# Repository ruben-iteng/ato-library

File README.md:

<!-- This document is autogenerated - Do not edit manually!! -->

# ato-library

This is a monorepo for various [ato](https://docs.atopile.io) and [fabll](https://docs.atopile.io/atopile/guides/faebryk) packages for your projects made with [atopile](https://www.github.com/atopile/atopile) that can be found in the official [atopile package registry](https://packages.atopile.io/)

## Available Packages

| Package | Modules | Description | Version |
|---------|---------|-------------|---------|
| [analog-devices-max14778](packages/analog-devices-max14778/README.md) | 1 module | Analog Devices MAX14778 dual 4:1 +/-25V above/below the rails analog multiplexer | 0.1.2 |
|  | analog_devices_max14778_driver | Analog Devices MAX14778 dual 4:1 +/-25V above/below the rails analog multiplexer | |
| [connectors](packages/connectors/README.md) | 4 modules | Miscellaneous connectors | 0.2.3 |
|  | dual_banana_connectors | Dual banana connectors (Red and Black) with 3/4\" (19.05mm) spacing. | |
|  | qwiic_vertical | Vertical QWIIC connector<br>    https://www.sparkfun.com/qwiic | |
|  | qwiic_horizontal | Horizontal QWIIC connector<br>    https://www.sparkfun.com/qwiic | |
|  | fan_connector | Connector for standard 4-pin 12v computer fans<br>    - 12V<br>    - Tach<br>    - PWM | |
| [dcdc-converters](packages/dcdc-converters/README.md) | 2 modules | DCDC converters | 0.2.2 |
|  | b0505s1wr3 | EVISUN B0505S-1WR3 5V to 5V isolated DCDC converter with shortcircuit protection<br>    - 5V input<br>    - 5V output<br>    - 1W power rating | |
|  | mpm3610-12vin-5vout | MPM3610 with component parameters optimized for 12V input and 5V output | |
| [debug-interfaces](packages/debug-interfaces/README.md) | 4 modules | SWD and tag connect headers for programming and debugging | 0.2.3 |
|  | arm_cortex_m_debug_header | 10 pin debug header with SWD pinout according to ARM Cortex M debug specification<br>    https://documentation-service.arm.com/static/5fce6c49e167456a35b36af1 | |
|  | swd_tc2030_idc_nl | Tag-Connect TC2030-IDC-NL (6-pin) landing pattern with SWD pinout | |
|  | swd_tc2030_idc_fp | Tag-Connect TC2030-IDC-FP (6-pin) landing pattern with SWD pinout | |
|  | segger_jlink_compact | SEGGER J-Link compact PCBA mount | |
| [esp32c3](packages/esp32c3/README.md) | 2 modules | ESP32 C3 microcontroller | 0.2.3 |
|  | esp32_c3_mini_driver | ESP32 S3 WROOM-1 module with build-in antenna and supporting components | |
|  | esp32_c3_mini_ufl_driver | ESP32 S3 WROOM-1 module with u.fl antenna connector and supporting components | |
| [esp32s3](packages/esp32s3/README.md) | 1 module | ESP32 S3 microcontroller | 0.2.2 |
|  | esp32_s3_wroom_driver | ESP32 S3 WROOM-1 module with build-in antenna and supporting components<br>    - 32MB flash<br>    - 2MB PSRAM | |
| [ina228](packages/ina228/README.md) | 1 module | INA228 low voltage power monitor with I2C interface | 0.2.2 |
|  | ina228 | INA228 85-V, 20-bit, ultra-precise, I2C output<br>    current/voltage/power/energy/charge monitor with alert | |
| [ldos](packages/ldos/README.md) | 1 module | Various Low Dropout Regulators (LDOs) | 0.2.3 |
|  | 5v_to_3v3 | 5V to 3.3V 600mA (max 1100mA) LDO | |
| [leds](packages/leds/README.md) | 2 modules | Various (addressable) LED components and modules | 0.2.2 |
|  | addressable_led_connector_driver | XT30 connector with 2 additional data pins.<br>    Wired for connecting to addressable LED strips. | |
|  | addressable_led_driver | Addressable LED with decoupling capacitors.<br><br>    Usage:<br>    from "ruben-iteng/ato-library/leds/addressable_leds.ato" import AddressableLED<br><br>    module MyProject:<br>        ...<br>        leds = new AddressableLED[3]<br><br>        power = new ElectricPower<br>        data_in = new ElectricLogic<br><br>        for led in leds:<br>            led -> WS2812B_5050_Black<br>            led.power ~ power<br><br>        data_in ~> leds[0] ~> leds[1] ~> leds[2] | |
| [logic](packages/logic/README.md) | 5 modules | Digital logic related components and modules | 0.2.2 |
|  | aip74lvc1t45_driver | Single channel bidirectional buffer.<br>    1.2V-5.5V logic levels.<br>    SOT-23-6 | |
|  | sn74lvc2g34dbvrumw_driver | UMWYoutai Semiconductor Co., Ltd.<br>    74LVC2G34 Dual buffer. | |
|  | sn74lvc3g14dc_driver | - | |
|  | iso1540_driver | ISO1540 low-power bidirectional I2C isolators.<br>    - 3.0V to 5.5V power and signal levels<br>    - up to 100Mhz I2C | |
|  | sn74cb3q3251pwr_driver | Texas Instruments SN74CB3Q3251PWR<br>    1 to/from 8 FET multiplexer/demultiplexer<br>    2.5V/3.3V low-voltage high-bandwidth bus switch | |
| [logos](packages/logos/README.md) | 1 module | Various logos | 0.2.0 |
|  | faebryk_logo_8x9mm | faebryk Logo 8x9mm | |
| [microchip-emc2101](packages/microchip-emc2101/README.md) | 1 module | Microchip EMC2101 fan driver | 0.1.2 |
|  | microchip_emc2101_driver | MicrochipEMC2101 fan driver<br>    Automatic Beta Compensation<br>    - Resistance Error Correction<br>    - Self-programming with available SMBus compatible EEPROM<br>    - Selectable PWM or DAC fan driver output<br>    - Temperature Monitors<br>      - External channel ±1°C accuracy<br>      - Internal channel ±2°C accuracy<br>    - 3.3 Volt Operation (5 Volt Tolerant Input Buffers)<br>    - SMBus 2.0 Compliant Interface, supports TIMEOUT | |
| [nxp_semiconductors-pca95xx](packages/nxp_semiconductors-pca95xx/README.md) | 7 modules | NXP Semiconductors PCA95xx family of I2C I/O expanders | 0.2.0 |
|  | pca9554pw_driver | NXP Semiconductors PCA9554 TSSOP16 package | |
|  | pca9554apw_driver | NXP Semiconductors PCA9554A TSSOP16 package | |
|  | pca9554abs_driver | NXP Semiconductors PCA9554A HVQFN16(4x4mm) package | |
|  | pca9554bs_driver | NXP Semiconductors PCA9554 HVQFN16(4x4mm) package | |
|  | pca9536d_driver | NXP Semiconductors PCA9536D SO-8 package | |
|  | pca9536tk_driver | NXP Semiconductors PCA9536TK HVSON-8 package | |
|  | pca9536dp_driver | NXP Semiconductors PCA9536DP TSSOP-8 package | |
| [relays](packages/relays/README.md) | 3 modules | Relay modules | 0.2.2 |
|  | driven_dpdt_bistable_relay | Bistable DPDT relay with driver and indicator LEDs<br>    - 5V coil power<br>    - 5V/3.3V logic power<br>    - 2A contact carry current<br>    - TC118S DC motor driver (H-bridge) as relay driver | |
|  | driven_dpdt_bistable_relay_push_terminal | DrivenDPDTBistableRelay with push terminal | |
|  | dc_motor_driver | Shenzhen Fuman Elec TC118S dc motor driver<br>    - Single-channel built-in high-power MOS full-bridge driver<br>    - Supports forward, reverse, stop, and brake functions<br>    - Built-in efficient thermal response and thermal protection<br>    - Low on-resistance (1.6Ω)<br>    - Maximum continuous output current: 1.8A, peak current: 2.5A | |
| [rohm_semiconductor_bh1750fvi](packages/rohm_semiconductor_bh1750fvi/README.md) | 1 module | ROHM Semiconductor BH1750FVI-TR Digital Ambient Light Sensor with I2C interface | 0.1.1 |
|  | bh1750_driver | Digital ambient light sensor with I2C interface<br><br>    - I2C bus Interface (f/s Mode Support)<br>    - Spectral responsibility is approximately human eye response<br>    - Illuminance to Digital Converter<br>    - Wide range and High resolution (1 - 65535 lx)<br>    - Low Current by power down function<br>    - 50Hz/60Hz Light noise reject-function<br>    - 1.8V Logic input interface<br>    - No need any external parts<br>    - Light source dependency is little (Incandescent Lamp, Fluorescent Lamp, Halogen Lamp, White LED, Sun Light)<br>    - It is possible to select 2 type of I2C slave-address<br>    - Adjustable measurement result for influence of optical window (It is possible to detect min. 0.11 lx, max. 100000 lx by using this function)<br>    - Small measurement variation (+/- 20%)<br>    - The influence of infrared is very small | |
| [rs485](packages/rs485/README.md) | 4 modules | RS485 related modules | 0.2.3 |
|  | bus_protection | RS485 bus protection.<br>    - Overvoltage protection<br>    - Overcurrent protection<br>    - Common mode filter<br>    - Termination resistor<br>    - ESD protection<br>    - Lightning protection<br><br>    based on: https://www.mornsun-power.com/public/uploads/pdf/TD(H)541S485H.pdf | |
|  | maxlinear_sp3485en_driver | Simple UART to RS485 converter.<br>    UART and write enable interface in, RS485 interface out. | |
|  | analog_devices_adm2587ebrwz_driver | Isolated UART to half duplex RS485 interface | |
|  | chipanalog_is2092a_driver | Isolated powered UART to RS485 transceiver design block.<br>    - 3.3V or 5V logic power<br>    - 3.3V or 5V module power<br>    - 0.5 Mbps UART<br>    - Read enable/write enable input<br>    - RS485 half duplex<br>    - ANSI/ESDA/JEDEC JS-001 ESD protection<br>    - JESD22-C101 CDM protection | |
| [switches](packages/switches/README.md) | 2 modules | Rotary encoders, switches, and other switch like components and modules | 0.1.4 |
|  | rotary_encoder_advanced | Rotary encoder + switchwith debouncing and hysteresis.<br><br>    Specialize the rotary encoder in your application:<br>    rot_encoder = new RotaryEncoderAdvanced<br>    rot_encoder.encoder -> ALPSALPINE_EC11E15244B2 | |
|  | test | Test module for buttons | |
| [texas_instruments_lm66200](packages/texas_instruments_lm66200/README.md) | 1 module | Texas Instruments LM66200DRLR 1.6 V to 5 V, 2.5-A Dual Ideal Diode With Automatic Switchover | 0.1.1 |
|  | lm66200 | Texas Instruments LM66200 dual ideal diode with automatic switchover.<br>    - Input voltage range: 1.6 V to 5.5 V<br>    - Maximum continuous current: 2.5 A<br>    - On-resistance: 40 mΩ (typical)<br>    - Standby current: 50 nA (typical)<br>    - Quiescent current: 1.32 μA (typical)<br>    - Automatic diode switchover<br>    - Controlled output slew rate:<br>        - 1.3 ms (typical) at 3.3 V.<br>    - Reverse current blocking when VOUT > VINx.<br>    - Thermal shutdown. | |
| [usb](packages/usb/README.md) | 4 modules | USB connectors and circuitry | 0.3.1 |
|  | usb_2_0_type_c_data_power_vertical_connector | USB 2.0 Type-C connector<br>    - 5V PD compatible<br>    - ESD protection<br>    - Fuse [500mA(hold), 1A(trip)]<br>    - Vertical USB Type-C connector | |
|  | usb_2_0_type_c_data_power_horizontal_connector | USB 2.0 Type-C connector<br>    - 5V PD compatible<br>    - ESD protection<br>    - Fuse [500mA(hold), 1A(trip)]<br>    - Horizontal USB Type-C connector | |
|  | usb_pd_power_sink_horizontal_connector | USB PD power sink with Horizontal Type-C connector<br><br>    Set the requested PD voltages as follows:<br>    9V  -> resistance = 6.8kohm<br>    12V -> resistance = 24kohm<br>    15V -> resistance = 56kohm<br>    20V -> resistance = DNP<br>    pd_sink = new USBPDPowerSink<br>    pd_sink.pd_trigger.voltage_set_resistor.resistance = 56kohm +/- 1% | |
|  | usb_pd_power_sink_vertical_connector | USB PD power sink with Vertical Type-C connector<br><br>    Set the requested PD voltages as follows:<br>    9V  -> resistance = 6.8kohm<br>    12V -> resistance = 24kohm<br>    15V -> resistance = 56kohm<br>    20V -> resistance = DNP<br>    pd_sink = new USBPDPowerSink<br>    pd_sink.pd_trigger.voltage_set_resistor.resistance = 56kohm +/- 1% | |

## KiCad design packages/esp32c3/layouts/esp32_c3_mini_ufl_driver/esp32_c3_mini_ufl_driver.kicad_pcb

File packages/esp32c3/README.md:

# esp32c3

ESP32 C3 microcontroller

## Package Information

- Version: 0.2.3
- Total Modules: 2
- Author(s): Ruben Baldewsing
- License: MIT
- Homepage: https://github.com/ruben-iteng/ato-library/blob/main/packages/esp32c3/README.md

## Available Modules

### Module List

| Image | Module | Description |
|-------|--------|-------------|
|| esp32_c3_mini_driver | ESP32 S3 WROOM-1 module with build-in antenna and supporting components |
|| esp32_c3_mini_ufl_driver | ESP32 S3 WROOM-1 module with u.fl antenna connector and supporting components |

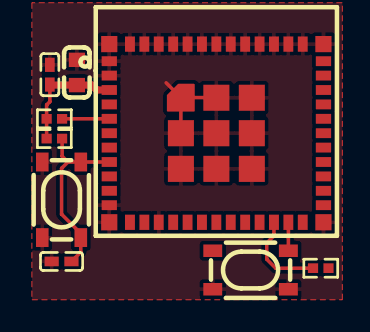
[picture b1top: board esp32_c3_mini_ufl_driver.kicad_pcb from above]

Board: 2 copper layers, 9 parts (0 on the bottom side), 6 nets.

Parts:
C1: 22µF ±20% 6.3V X5R; C0603
C2: 100nF ±10% 16V X7R; C0402
C3: 1µF ±10% 25V X5R; C0402
R1, R2, R3: 10kΩ ±1% 62.5mW; R0402
U1, U3: KEY-SMD_4P-L4.2-W3.2-P2.20-LS4.6
U2: WIFIM-SMD_ESP32-C3-MINI-MINI-1U

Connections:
EN: C3.1, R3.2, U2.8, U3.1, U3.2
IO2: R1.1, U2.5
IO9: U1.1, U1.2, U2.23
gnd: C1.2, C2.2, C3.2, U1.3, U1.4, U2.1, U2.2, U2.11, U2.14, U2.36, U2.37, U2.38, U2.39, U2.40, U2.41, U2.42, U2.43, U2.44, U2.45, U2.46, U2.47, U2.48, U2.49, U2.50, U2.51, U2.52, U2.53, U3.3, U3.4
hv: C1.1, C2.1, R1.2, R2.2, R3.1, U2.3
line: R2.1, U2.22

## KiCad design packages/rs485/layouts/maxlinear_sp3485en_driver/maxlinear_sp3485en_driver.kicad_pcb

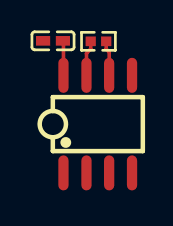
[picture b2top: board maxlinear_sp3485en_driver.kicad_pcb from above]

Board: 2 copper layers, 3 parts (0 on the bottom side), 4 nets.

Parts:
C1: 100nF ±10% 16V X7R; C0402
R1: 120Ω ±1% 62.5mW; R0402
U1: SOIC-8_L5.0-W4.0-P1.27-LS6.0-BL

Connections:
A: R1.1, U1.6
B: R1.2, U1.7
VCC: C1.1, U1.8
gnd: C1.2, U1.5

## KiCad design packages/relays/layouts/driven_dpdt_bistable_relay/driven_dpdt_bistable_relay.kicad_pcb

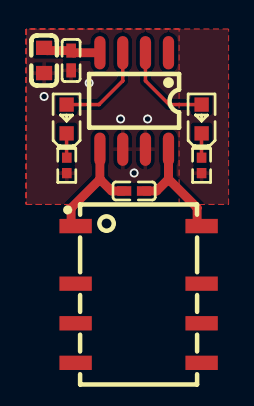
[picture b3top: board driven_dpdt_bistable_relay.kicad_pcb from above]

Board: 2 copper layers, 9 parts (0 on the bottom side), 8 nets.

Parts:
C1: 100nF ±10% 16V X7R; C0402
C2: 4.7µF ±10% 16V X5R; C0603
C3: 100pF ±5% 50V C0G; C0402
LED1, LED2: LED0603-RD
R1, R2: 10kΩ ±1% 62.5mW; R0402
U1: SOP-8_L4.9-W3.9-P1.27-LS6.0-BL
U2: RELAY-SMD_G6KU-2F-Y

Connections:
OUTA: C3.1, U1.8, U2.8
anode: LED2.2, U1.3
anode-1: LED1.2, U1.2
cathode: LED2.1, R2.1
cathode-1: LED1.1, R1.1
gnd: C1.2, C2.2, R1.2, R2.2, U1.6, U1.7
gnd-1: C3.2, U1.5, U2.1
hv: C1.1, C2.1, U1.4

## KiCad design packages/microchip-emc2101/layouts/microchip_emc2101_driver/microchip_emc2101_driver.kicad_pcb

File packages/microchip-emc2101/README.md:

# microchip-emc2101

Microchip EMC2101 fan driver

## Package Information

- Version: 0.1.2
- Total Modules: 1
- Author(s): Ruben Baldewsing
- License: MIT
- Homepage: https://github.com/ruben-iteng/ato-library/blob/main/packages/microchip-emc2101/README.md

## Available Modules

### Module List

| Image | Module | Description |
|-------|--------|-------------|
|| microchip_emc2101_driver | MicrochipEMC2101 fan driver<br>    Automatic Beta Compensation<br>    - Resistance Error Correction<br>    - Self-programming with available SMBus compatible EEPROM<br>    - Selectable PWM or DAC fan driver output<br>    - Temperature Monitors<br>      - External channel ±1°C accuracy<br>      - Internal channel ±2°C accuracy<br>    - 3.3 Volt Operation (5 Volt Tolerant Input Buffers)<br>    - SMBus 2.0 Compliant Interface, supports TIMEOUT |

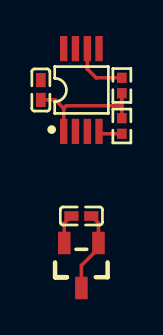
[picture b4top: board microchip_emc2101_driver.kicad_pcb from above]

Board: 2 copper layers, 6 parts (0 on the bottom side), 6 nets.

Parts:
C1: 100nF ±10% 16V X7R; C0402
C2: 2.2nF ±10% 50V X7R; C0402
Q1: SOT-23-3_L2.9-W1.3-P1.90-LS2.4-TR
R1, R2: 10kΩ ±1% 62.5mW; R0402
U1: MSOP-8_L3.0-W3.0-P0.65-LS4.9-BL

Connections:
DN: C2.1, Q1.2, Q1.3, U1.3
DP: C2.2, Q1.1, U1.2
FAN: R1.1, U1.4
VDD: C1.1, R1.2, R2.2, U1.1
gnd: C1.2, U1.5
nALERT_TACH: R2.1, U1.6

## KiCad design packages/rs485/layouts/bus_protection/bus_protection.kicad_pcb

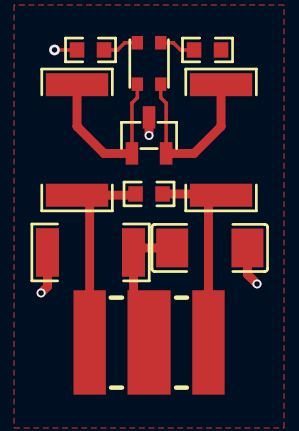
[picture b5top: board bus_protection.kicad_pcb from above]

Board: 2 copper layers, 10 parts (0 on the bottom side), 8 nets.

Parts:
C1: 1nF ±10% 2kV X7R; C1808
FL1: FILTER-SMD_4P-L2.5-W2.0-BL
GDT1: DIO-DT-SMD_L7.2-W5.0
R1, R2: 2.7Ω ±5% 1W; R2512
R3: 1MΩ ±1% 750mW; R2010
R4, R5: 390Ω ±1% 100mW; R0603
R6: 120Ω ±1% 100mW; R0603
U1: SOT-23-3_L2.9-W1.3-P1.90-LS2.4-BR

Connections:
earth: C1.2, GDT1.2, R3.2
gnd: C1.1, R3.1, R5.2, U1.3
line: FL1.4, R5.1
line-1: FL1.2, R1.1, U1.2
line-2: FL1.3, R4.1
line-3: FL1.1, R2.1, U1.1
tube_1: GDT1.1, R2.2, R6.1
tube_2: GDT1.3, R1.2, R6.2

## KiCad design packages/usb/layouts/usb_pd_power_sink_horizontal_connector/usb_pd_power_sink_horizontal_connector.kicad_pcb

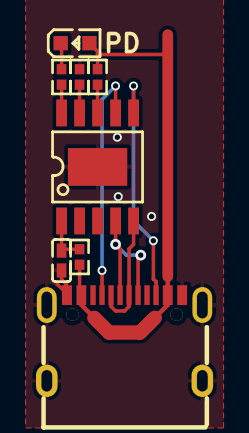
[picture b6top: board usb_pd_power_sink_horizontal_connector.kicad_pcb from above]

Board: 2 copper layers, 8 parts (0 on the bottom side), 11 nets.

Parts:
C1: 1µF ±10% 25V X5R; C0402
LED1: LED0603-RD
R1, R2, R4: 10kΩ ±1% 62.5mW; R0402
R3: 1kΩ ±1% 62.5mW; R0402
U1: ESSOP-10_L4.9-W3.9-P1.0-LS6.0-TL-EP
X1: USB-C-SMD_TYPE-C-6PIN-2MD-073

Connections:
anode: LED1.2, R2.1, R3.1, X1.2, X1.11
cathode: LED1.1, R1.1
gnd: C1.2, R4.2, U1.11, X1.1, X1.12, X1.13, X1.14
hv: C1.1, R3.2, U1.1
line: U1.7, X1.4
line-1: U1.6, X1.10
line-4: U1.5, X1.5, X1.7
line-5: U1.4, X1.6, X1.8
pd_trigger-gnd: R1.2, U1.10
pd_trigger-line: R4.1, U1.9
pd_trigger-line-1: R2.2, U1.8

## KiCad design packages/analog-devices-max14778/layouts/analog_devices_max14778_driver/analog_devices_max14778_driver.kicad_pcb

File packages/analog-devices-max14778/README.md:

# analog-devices-max14778

Analog Devices MAX14778 dual 4:1 +/-25V above/below the rails analog multiplexer

## Package Information

- Version: 0.1.2
- Total Modules: 1
- Author(s): Ruben Baldewsing
- License: MIT
- Homepage: https://github.com/ruben-iteng/ato-library/blob/main/packages/analog-devices-max14778/README.md

## Available Modules

### Module List

| Image | Module | Description |
|-------|--------|-------------|
|| analog_devices_max14778_driver | Analog Devices MAX14778 dual 4:1 +/-25V above/below the rails analog multiplexer |

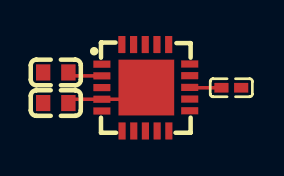
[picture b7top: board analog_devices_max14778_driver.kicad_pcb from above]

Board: 2 copper layers, 4 parts (0 on the bottom side), 4 nets.

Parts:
C1: 100nF ±10% 16V X7R; C0402
C2, C3: 100nF ±10% 100V X7R; C0603
U1: TQFN-20_L5.0-W5.0-P0.65-TL-EP3.1

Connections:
EP: C2.1, U1.4, U1.21
VP: C3.1, U1.2
gnd: C1.2, C2.2, C3.2, U1.3
hv: C1.1, U1.13

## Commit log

2025-04-13 Setup basics
2025-04-13 Add relays package
2025-04-13 Add build all script from atopile/packages
2025-04-13 Add debug connectors package
2025-04-13 Use Jinja2 for README template
    - Auto gen package readme
2025-04-13 Add package info to README
2025-04-18 Add explanation of the hooks
2025-04-18 Parse docstrings of python based modules
2025-04-18 Add new packages
    - debug interfaces
    - connectors
    - ina228
    - rs485
    - relays
2025-04-22 Bump required atopile version
2025-04-22 Fix pulldown on RE pins
2025-04-22 ignore more common files and artifacts
2025-04-22 Add logo package
2025-04-22 Add LDOs package
2025-04-22 Add USB2.0 Type-C interface to connector package
2025-04-22 Update build script and regenerate outputs
2025-04-27 Add ESP32S3, BM9002, Logic; Various naming updates and splitting of packages
2025-04-27 Add image rendering
2025-04-27 Fix pre-commit hook to run with uv
2025-04-27 Fix files to run hook on
2025-04-27 Generate images and READMEs
2025-04-27 Also regenerate READMEs when md templates changed
2025-04-27 Don't generate board renders with pre-commit hook.
    Then change every time they are generated
2025-04-27 Fix image size
2025-04-29 Update author name
2025-04-29 Remove connectors and replace with leds package
2025-04-29 rename bm9002 package
2025-04-29 Build all packages without designators on silkscreen.
    Also disable fail_on_drc and enable keep_picked_parts for build
2025-04-29 Change to alpha version
2025-04-29 Update version
2025-04-29 Add publishing workflow
2025-04-29 Update templates with abs reference to images as a short-term hack for getting them in the package manager
2025-04-29 Update READMEs
2025-05-01 Remove pull resistor (should not be part of the tranceiver)
2025-05-01 Fix publish if build fails
2025-05-01 Fix publish on failed build & fix pull resistor that should not be there (#2)
    * Remove pull resistor (should not be part of the tranceiver)
    * Fix publish if build fails
2025-05-01 [Publish] Fix image links and rebuild
2025-05-01 Don't run the workflow on draft PRs
2025-05-02 Bump version
2025-05-02 Rebuild modules
2025-05-02 Generate documentation
2025-05-02 Work around bad atopile net handling
    Mannually remove net number gap in pcb file and rebuild
2025-05-02 try with keep netnames enabled
2025-05-02 Don't run the workflow on draft PRs (#4)
2025-05-02 [Publish] Rebuild modules (with no dep on upstream atopile pr) (#5)
    * Fixes image link on published packages
2025-05-02 Add DrivenDPDTBistableRelayScrewTerminal
2025-05-05 Add seperate manually triggered publish workflow. Build workflow always runs (except on draft PR)
2025-05-06 Add seperate manually triggered publish workflow. Build workflow always runs (except on draft PR) (#7)
2025-05-06 Change name and update layout
2025-05-06 [Publish] Driven DPDT bistable-relay with push in terminal (#6)
2025-05-06 Add Rotaty encoder with signal cleaning, I2C isolator, and logic schmitt trigger
2025-05-06 Add Rotaty encoder with signal cleaning, I2C isolator, and logic schmitt trigger (#8)
2025-05-09 Add USB PD trigger
2025-05-09 Add USB PD trigger (#9)
2025-05-09 Update with new ato 0.7.x features
2025-05-09 Update with new ato 0.7.x features (#10)
2025-05-09 Add various addressable LEDs
2025-05-09 Add various addressable LEDs (#11)
2025-05-09 Rebuild logic package
2025-05-09 Add updated docs for logic package
2025-05-09 Rebuild relays package
2025-05-09 Rebuild usb package
2025-05-09 Rebuild switches package
2025-05-09 Rebuild rs485 package
2025-05-09 Add option to specify package to doc generator
2025-05-09 Add updated docs for rs485 package
2025-05-09 Update main README
2025-05-09 Rebuild modules frozen (#12)
    * Rebuild logic package
    * Add updated docs for logic package
    * Rebuild relays package
    * Rebuild usb package
    * Rebuild switches package
    * Rebuild rs485 package
2025-05-10 Use markdown instead of html for images in READMEs
2025-05-10 Regenerate READMEs and bump versions
2025-05-10 Fix: images for package registry (#13)
    * Use markdown instead of html for images in READMEs
    * Regenerate READMEs and bump versions
2025-05-10 Add DCDC converters package
2025-05-10 Add misc connectors package
2025-05-11 Update LDOs package
2025-05-11 Add QWIIC to connector package
2025-05-11 Add dual buffer to logic package
2025-05-12 add missing connection and remove test file
2025-05-12 Clean up package
2025-05-12 Update logos package
2025-05-12 Update RS485 protection layout
2025-05-12 Update rotary encoder advanced layout
2025-05-12 Update switches package readme
2025-05-12 Add various new packages (#14)
    Add:
    - DCDC converters
    - Connectors
    Update:
    - logic
    - add dual buffer
2025-05-12 Fix missing connection between JTAG and reset (enable)
2025-05-12 Fix missing connection between JTAG and reset (enable) (#15)
2025-05-13 Add isolated and powered RS485 tranceiver
2025-05-13 Add isolated and powered RS485 tranceiver (#16)
2025-05-13 Add ESP32C3 package
2025-05-13 Connect extra gnd pins
2025-05-14 Add ESP32C3 package 📦 (#17)
2025-05-16 Add SN74CB3Q3251PWR (de)mux
2025-05-16 Add SN74CB3Q3251PWR (de)muxer (#18)
2025-05-17 Add NXP PCA95xx series package
2025-05-18 Add Analog Devices MAX14778 package
2025-05-18 run for any push to the main branch or when a pull request is opened or updated
2025-05-18 run for any push to the main branch or when a pull request is opened or updated (#19)
2025-05-18 Remove unpublished package
2025-05-18 Convert B0505 into ato
2025-05-18 Fix INA228 package
2025-05-18 Run precommit
2025-05-18 Update images
2025-05-18 Remove unpublished package and fix INA228 and DCDC package (#22)
    * Remove unpublished package
    * Convert B0505 into ato
    * Fix INA228 package
    * Run precommit
    * Update READMEs
    * Update images
2025-05-18 Add NXP PCA95xx series package (#20)
    * Add NXP PCA95xx series package
2025-05-18 Fix whitespace
2025-05-18 Add Analog Devices MAX14778 package (#21)
2025-05-18 Update packages:
    - requited
    - package > driver method
    - cleaning up
    - aligning packages
2025-05-18 Rebuild all
2025-05-18 Cleaning-up and updating to latest standards (#23)
    * Update packages:
    - add required flag
    - package > driver method
    - cleaning up
    - aligning packages
    * Rebuild all
2025-05-18 Fix missing images
2025-05-18 Fix frozen build
2025-05-18 Fix missing images (#24)
2025-05-20 Add Fan connector and interface
2025-05-20 Add microchip EMC2101 fan driver
    Generate docs
2025-05-20 Add fan connector and controller packages (#25)
    * Add Fan connector and interface
    * Add microchip EMC2101 fan driver
2025-05-21 Fix wrong logic reference. Split driver into own module
2025-05-21 Generate docs
2025-05-21 Fix bistable relay (#26)
    * Fix wrong logic reference.
    * Split driver into own module
2025-05-21 Fix LDO power in voltage range
    Fix RS485 sp3485 and is2092 RE WE connections
2025-05-21 Fix LDO power in voltage range (#27)
2025-05-23 Add basic layout and footprint
2025-05-23 Add header and docs
2025-05-23 Add reference of CAD file
2025-05-24 Add J-Link compact footprint (#28)
2025-05-24 Add MPM3610 DCDC converter
2025-05-24 Add MPM3610 DCDC converter (#29)
2025-05-24 Fix homepage links and bump versions
2025-05-24 Update docs
    Fix segger component > module
2025-05-24 Fix homepage links and bump versions (#30)
    Fix segger component > module
2025-05-25 Add Texas Instruments LM66200 double ideal diode package
2025-05-25 Add Texas Instruments LM66200 double ideal diode package (#31)
2025-05-25 ESP32C3 fix USB connection
2025-05-25 ESP32C3 fix USB connection (#32)
2025-05-30 Add vertical usb connector option
2025-05-30 Add vertical usb connector option (#33)
2025-05-30 Add rohm_semiconductor_bh1750fvi
2025-05-30 Add rohm_semiconductor_bh1750fvi (#34)
2025-06-03 Temp use specific ato version to be able to publish
    Pre 0.9.x
2025-06-03 Temp change the ato version in build stage
2025-06-03 Fix tag
2025-06-03 Fix hash
2025-06-03 Temp use specific ato version (#35)
    * Temp use specific ato version to be able to publish Pre 0.9.x packages
2025-06-08 Add the parts lib to git
2025-06-08 Update analog_devices_max14778
2025-06-08 WIP update dcdc converters
2025-06-08 WIP update connectors
2025-06-08 WIP update debug-interfaces
2025-06-08 WIP update esp32c3
2025-06-08 WIP update ina228
2025-06-08 WIP update LDOs
2025-06-08 WIP update LEDs
2025-06-08 WIP update logic
2025-06-08 WIP update emc2101
2025-06-08 WIP update pca95xx
2025-06-08 WIP update relays
2025-06-08 WIP update rs485
2025-06-08 WIP update switches
2025-06-08 WIP update lm66200
2025-06-08 WIP update usb
2025-06-10 WIP update packages till ESPs
2025-06-17 Manually fix fp lib tables
    fix some small bugs
    fix package only modules (e.g. logos)
2025-06-17 Update 3D model locations
    fix missing renders
2025-06-17 Switch to main ato branch for build workflow
2025-06-17 Switch to main auto version for publish workflow
2025-06-23 rebuild all packages & regenerate images of changed layouts (silk)
    Add new scripts for version bump and build (based on atopile/packages)
2025-06-23 Add missing fp-lib-tables
2025-06-26 Fix banana connectors
2025-06-26 remove indicator leds (duplicate from atopile/indicator-leds)
2025-06-26 fix rs485 frozen build
2025-06-26 fix lm66200 frozen build
2025-06-26 fix ldo frozen build
2025-06-27 fix SN74CB3Q3251PWR frozen build
2025-06-27 Use official indicator-led package
2025-06-27 fix import name
2025-06-27 Fix fan connector
2025-06-27 Use packages from packages folder
2025-06-28 Update packages to ato v0.9.x (#36)
2025-06-28 fix(workflow): publish: ato version duplicate
2025-06-28 fix(workflow): publish: ato version duplicate (#37)
2025-06-28 fix(esp32c3): frozen build & unconnected pads
2025-06-28 fix(esp32c3): frozen build & unconnected pads (#38)
